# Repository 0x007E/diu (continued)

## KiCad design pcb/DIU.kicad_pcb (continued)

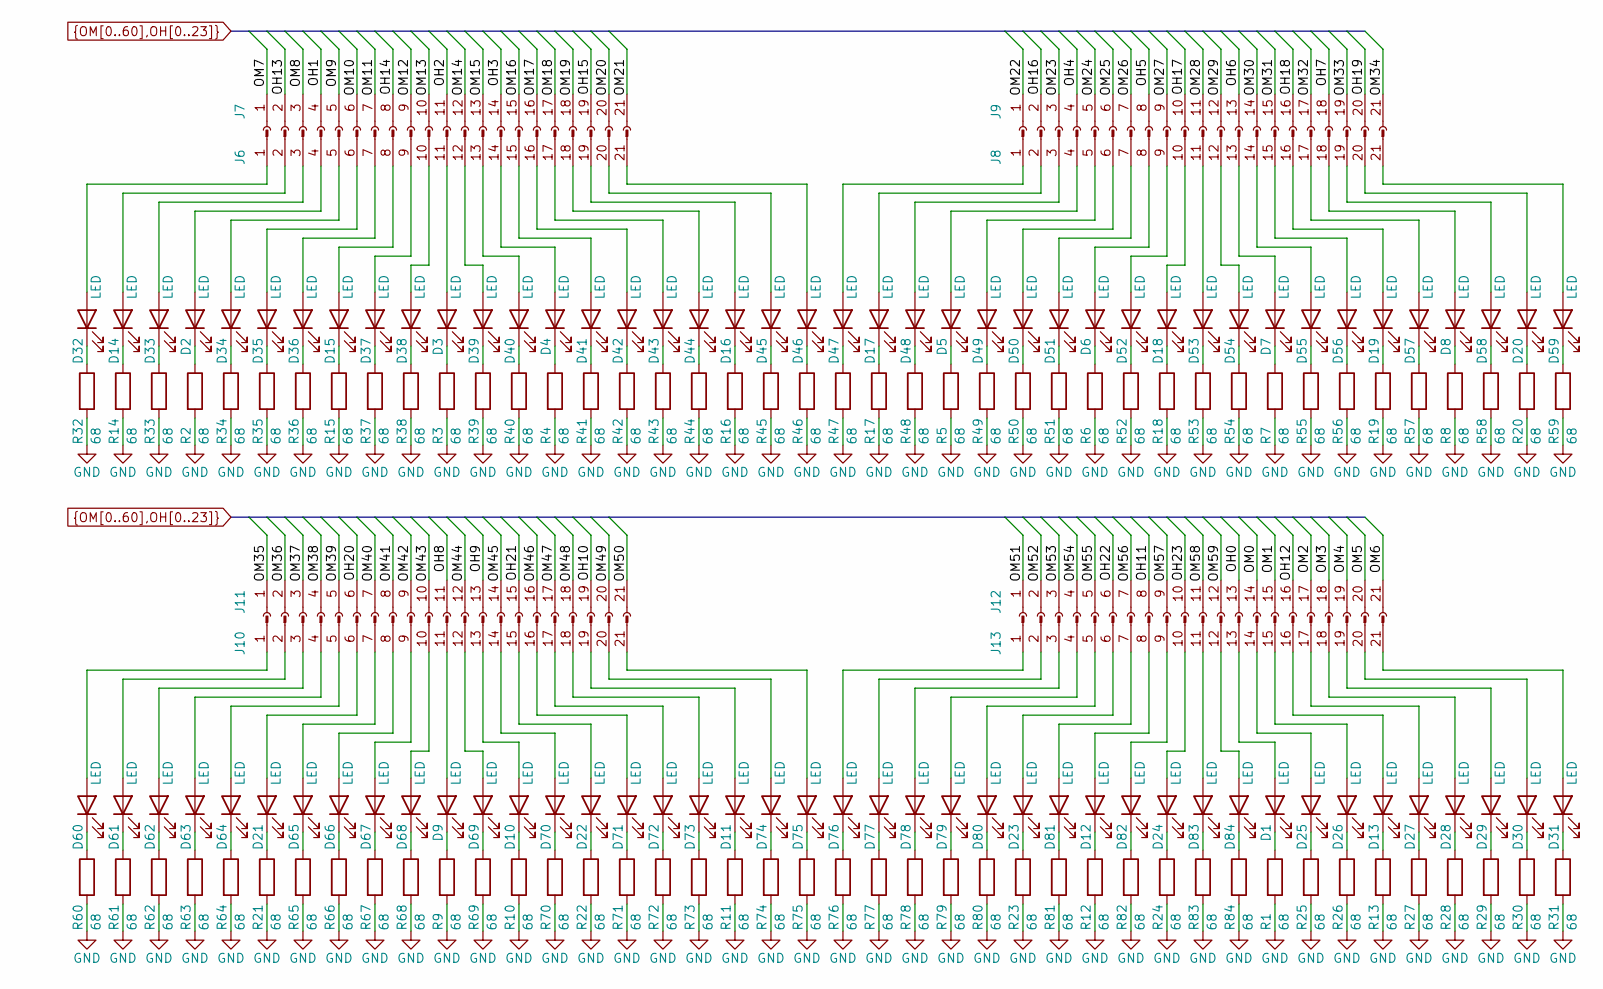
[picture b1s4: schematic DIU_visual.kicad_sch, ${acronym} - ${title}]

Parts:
D1, D2, D3, D4, D5, D6, D7, D8, D9, D10, D11, D12, D13, D14, D15, D16, D17, D18, D19, D20, D21, D22, D23, D24, D25, D26, D27, D28, D29, D30, D31, D32, D33, D34, D35, D36, D37, D38, D39, D40, D41, D42, D43, D44, D45, D46, D47, D48, D49, D50, D51, D52, D53, D54, D55, D56, D57, D58, D59, D60, D61, D62, D63, D64, D65, D66, D67, D68, D69, D70, D71, D72, D73, D74, D75, D76, D77, D78, D79, D80, D81, D82, D83, D84: LED; LED_1206_3216Metric
J6, J8, J10, J13: Conn_01x21_Pin; PinHeader_1x21_P2.54mm_Vertical
J7, J9, J11, J12: Conn_01x21_Socket; PinSocket_1x21_P2.54mm_Vertical
R1, R2, R3, R4, R5, R6, R7, R8, R9, R10, R11, R12, R13, R14, R15, R16, R17, R18, R19, R20, R21, R22, R23, R24, R25, R26, R27, R28, R29, R30, R31, R32, R33, R34, R35, R36, R37, R38, R39, R40, R41, R42, R43, R44, R45, R46, R47, R48, R49, R50, R51, R52, R53, R54, R55, R56, R57, R58, R59, R60, R61, R62, R63, R64, R65, R66, R67, R68, R69, R70, R71, R72, R73, R74, R75, R76, R77, R78, R79, R80, R81, R82, R83, R84: 68; R_1206_3216Metric

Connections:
GND: R1.2, R2.2, R3.2, R4.2, R5.2, R6.2, R7.2, R8.2, R9.2, R10.2, R11.2, R12.2, R13.2, R14.2, R15.2, R16.2, R17.2, R18.2, R19.2, R20.2, R21.2, R22.2, R23.2, R24.2, R25.2, R26.2, R27.2, R28.2, R29.2, R30.2, R31.2, R32.2, R33.2, R34.2, R35.2, R36.2, R37.2, R38.2, R39.2, R40.2, R41.2, R42.2, R43.2, R44.2, R45.2, R46.2, R47.2, R48.2, R49.2, R50.2, R51.2, R52.2, R53.2, R54.2, R55.2, R56.2, R57.2, R58.2, R59.2, R60.2, R61.2, R62.2, R63.2, R64.2, R65.2, R66.2, R67.2, R68.2, R69.2, R70.2, R71.2, R72.2, R73.2, R74.2, R75.2, R76.2, R77.2, R78.2, R79.2, R80.2, R81.2, R82.2, R83.2, R84.2; also elsewhere on the board
unnamed: D1.2 (A), J13.13
unnamed: D1.1 (K), R1.1
unnamed: D2.2 (A), J6.4
unnamed: D2.1 (K), R2.1
unnamed: D3.2 (A), J6.11
unnamed: D3.1 (K), R3.1
unnamed: D4.2 (A), J6.14
unnamed: D4.1 (K), R4.1
unnamed: D5.2 (A), J8.4
unnamed: D5.1 (K), R5.1
unnamed: D6.2 (A), J8.8
unnamed: D6.1 (K), R6.1
unnamed: D7.2 (A), J8.13
unnamed: D7.1 (K), R7.1
unnamed: D8.2 (A), J8.18
unnamed: D8.1 (K), R8.1
unnamed: D9.2 (A), J10.11
unnamed: D9.1 (K), R9.1
unnamed: D10.2 (A), J10.13
unnamed: D10.1 (K), R10.1
unnamed: D11.2 (A), J10.19
unnamed: D11.1 (K), R11.1
unnamed: D12.2 (A), J13.8
unnamed: D12.1 (K), R12.1
unnamed: D13.2 (A), J13.16
unnamed: D13.1 (K), R13.1
unnamed: D14.2 (A), J6.2
unnamed: D14.1 (K), R14.1
unnamed: D15.2 (A), J6.8
unnamed: D15.1 (K), R15.1
unnamed: D16.2 (A), J6.19
unnamed: D16.1 (K), R16.1
unnamed: D17.2 (A), J8.2
unnamed: D17.1 (K), R17.1
unnamed: D18.2 (A), J8.10
unnamed: D18.1 (K), R18.1
unnamed: D19.2 (A), J8.16
unnamed: D19.1 (K), R19.1
unnamed: D20.2 (A), J8.20
unnamed: D20.1 (K), R20.1
unnamed: D21.2 (A), J10.6
unnamed: D21.1 (K), R21.1
unnamed: D22.2 (A), J10.15
unnamed: D22.1 (K), R22.1
unnamed: D23.2 (A), J13.6
unnamed: D23.1 (K), R23.1
unnamed: D24.2 (A), J13.10
unnamed: D24.1 (K), R24.1
unnamed: D25.2 (A), J13.14
unnamed: D25.1 (K), R25.1
unnamed: D26.2 (A), J13.15
unnamed: D26.1 (K), R26.1
unnamed: D27.2 (A), J13.17
unnamed: D27.1 (K), R27.1
unnamed: D28.2 (A), J13.18
unnamed: D28.1 (K), R28.1
unnamed: D29.2 (A), J13.19
unnamed: D29.1 (K), R29.1
unnamed: D30.2 (A), J13.20
unnamed: D30.1 (K), R30.1
unnamed: D31.2 (A), J13.21
unnamed: D31.1 (K), R31.1
unnamed: D32.2 (A), J6.1
unnamed: D32.1 (K), R32.1
unnamed: D33.2 (A), J6.3
unnamed: D33.1 (K), R33.1
unnamed: D34.2 (A), J6.5
unnamed: D34.1 (K), R34.1
unnamed: D35.2 (A), J6.6
unnamed: D35.1 (K), R35.1
unnamed: D36.2 (A), J6.7
unnamed: D36.1 (K), R36.1
unnamed: D37.2 (A), J6.9
unnamed: D37.1 (K), R37.1
unnamed: D38.2 (A), J6.10
unnamed: D38.1 (K), R38.1
unnamed: D39.2 (A), J6.12
unnamed: D39.1 (K), R39.1
unnamed: D40.2 (A), J6.13
unnamed: D40.1 (K), R40.1
unnamed: D41.2 (A), J6.15
unnamed: D41.1 (K), R41.1
unnamed: D42.2 (A), J6.16
unnamed: D42.1 (K), R42.1
unnamed: D43.2 (A), J6.17
unnamed: D43.1 (K), R43.1
unnamed: D44.2 (A), J6.18
unnamed: D44.1 (K), R44.1
unnamed: D45.2 (A), J6.20
unnamed: D45.1 (K), R45.1
unnamed: D46.2 (A), J6.21
unnamed: D46.1 (K), R46.1
unnamed: D47.2 (A), J8.1
unnamed: D47.1 (K), R47.1
unnamed: D48.2 (A), J8.3
unnamed: D48.1 (K), R48.1
unnamed: D49.2 (A), J8.5
unnamed: D49.1 (K), R49.1
unnamed: D50.2 (A), J8.6
unnamed: D50.1 (K), R50.1
unnamed: D51.2 (A), J8.7
unnamed: D51.1 (K), R51.1
unnamed: D52.2 (A), J8.9
unnamed: D52.1 (K), R52.1
unnamed: D53.2 (A), J8.11
unnamed: D53.1 (K), R53.1
unnamed: D54.2 (A), J8.12
unnamed: D54.1 (K), R54.1
unnamed: D55.2 (A), J8.14
unnamed: D55.1 (K), R55.1
unnamed: D56.2 (A), J8.15
unnamed: D56.1 (K), R56.1
unnamed: D57.2 (A), J8.17
unnamed: D57.1 (K), R57.1
unnamed: D58.2 (A), J8.19
unnamed: D58.1 (K), R58.1
unnamed: D59.2 (A), J8.21
unnamed: D59.1 (K), R59.1
unnamed: D60.2 (A), J10.1
unnamed: D60.1 (K), R60.1
unnamed: D61.2 (A), J10.2
unnamed: D61.1 (K), R61.1
unnamed: D62.2 (A), J10.3
unnamed: D62.1 (K), R62.1
unnamed: D63.2 (A), J10.4
unnamed: D63.1 (K), R63.1
unnamed: D64.2 (A), J10.5
unnamed: D64.1 (K), R64.1
unnamed: D65.2 (A), J10.7
unnamed: D65.1 (K), R65.1
unnamed: D66.2 (A), J10.8
unnamed: D66.1 (K), R66.1
unnamed: D67.2 (A), J10.9
unnamed: D67.1 (K), R67.1
unnamed: D68.2 (A), J10.10
unnamed: D68.1 (K), R68.1
unnamed: D69.2 (A), J10.12
unnamed: D69.1 (K), R69.1
unnamed: D70.2 (A), J10.14
unnamed: D70.1 (K), R70.1
unnamed: D71.2 (A), J10.16
unnamed: D71.1 (K), R71.1
unnamed: D72.2 (A), J10.17
unnamed: D72.1 (K), R72.1
unnamed: D73.2 (A), J10.18
unnamed: D73.1 (K), R73.1
unnamed: D74.2 (A), J10.20
unnamed: D74.1 (K), R74.1
unnamed: D75.2 (A), J10.21
unnamed: D75.1 (K), R75.1
unnamed: D76.2 (A), J13.1
unnamed: D76.1 (K), R76.1
unnamed: D77.2 (A), J13.2
unnamed: D77.1 (K), R77.1
unnamed: D78.2 (A), J13.3
unnamed: D78.1 (K), R78.1
unnamed: D79.2 (A), J13.4
unnamed: D79.1 (K), R79.1
unnamed: D80.2 (A), J13.5
unnamed: D80.1 (K), R80.1
unnamed: D81.2 (A), J13.7
unnamed: D81.1 (K), R81.1
unnamed: D82.2 (A), J13.9
unnamed: D82.1 (K), R82.1
unnamed: D83.2 (A), J13.11
unnamed: D83.1 (K), R83.1
unnamed: D84.2 (A), J13.12
unnamed: D84.1 (K), R84.1
OH0: J12.13; also elsewhere on the board
OH1: J7.4; also elsewhere on the board
OH2: J7.11; also elsewhere on the board
OH3: J7.14; also elsewhere on the board
OH4: J9.4; also elsewhere on the board
OH5: J9.8; also elsewhere on the board
OH6: J9.13; also elsewhere on the board
OH7: J9.18; also elsewhere on the board
OH8: J11.11; also elsewhere on the board
OH9: J11.13; also elsewhere on the board
OH10: J11.19; also elsewhere on the board
OH11: J12.8; also elsewhere on the board
OH12: J12.16; also elsewhere on the board
OH13: J7.2; also elsewhere on the board
OH14: J7.8; also elsewhere on the board
OH15: J7.19; also elsewhere on the board
OH16: J9.2; also elsewhere on the board
OH17: J9.10; also elsewhere on the board
OH18: J9.16; also elsewhere on the board
OH19: J9.20; also elsewhere on the board
OH20: J11.6; also elsewhere on the board
OH21: J11.15; also elsewhere on the board
OH22: J12.6; also elsewhere on the board
OH23: J12.10; also elsewhere on the board
OM0: J12.14; also elsewhere on the board
OM1: J12.15; also elsewhere on the board
OM2: J12.17; also elsewhere on the board
OM3: J12.18; also elsewhere on the board
OM4: J12.19; also elsewhere on the board
OM5: J12.20; also elsewhere on the board
OM6: J12.21; also elsewhere on the board
OM7: J7.1; also elsewhere on the board
OM8: J7.3; also elsewhere on the board
OM9: J7.5; also elsewhere on the board
OM10: J7.6; also elsewhere on the board
OM11: J7.7; also elsewhere on the board
OM12: J7.9; also elsewhere on the board
OM13: J7.10; also elsewhere on the board
OM14: J7.12; also elsewhere on the board
OM15: J7.13; also elsewhere on the board
OM16: J7.15; also elsewhere on the board
OM17: J7.16; also elsewhere on the board
OM18: J7.17; also elsewhere on the board
OM19: J7.18; also elsewhere on the board
OM20: J7.20; also elsewhere on the board
OM21: J7.21; also elsewhere on the board
OM22: J9.1; also elsewhere on the board
OM23: J9.3; also elsewhere on the board
OM24: J9.5; also elsewhere on the board
OM25: J9.6; also elsewhere on the board
OM26: J9.7; also elsewhere on the board
OM27: J9.9; also elsewhere on the board
OM28: J9.11; also elsewhere on the board
OM29: J9.12; also elsewhere on the board
OM30: J9.14; also elsewhere on the board
OM31: J9.15; also elsewhere on the board
OM32: J9.17; also elsewhere on the board
OM33: J9.19; also elsewhere on the board
OM34: J9.21; also elsewhere on the board
OM35: J11.1; also elsewhere on the board
OM36: J11.2; also elsewhere on the board
OM37: J11.3; also elsewhere on the board
OM38: J11.4; also elsewhere on the board
OM39: J11.5; also elsewhere on the board
OM40: J11.7; also elsewhere on the board
OM41: J11.8; also elsewhere on the board
OM42: J11.9; also elsewhere on the board
OM43: J11.10; also elsewhere on the board
OM44: J11.12; also elsewhere on the board
OM45: J11.14; also elsewhere on the board
OM46: J11.16; also elsewhere on the board
OM47: J11.17; also elsewhere on the board
OM48: J11.18; also elsewhere on the board
OM49: J11.20; also elsewhere on the board
OM50: J11.21; also elsewhere on the board
OM51: J12.1; also elsewhere on the board
OM52: J12.2; also elsewhere on the board
OM53: J12.3; also elsewhere on the board
OM54: J12.4; also elsewhere on the board
OM55: J12.5; also elsewhere on the board
OM56: J12.7; also elsewhere on the board
OM57: J12.9; also elsewhere on the board
OM58: J12.11; also elsewhere on the board
OM59: J12.12; also elsewhere on the board

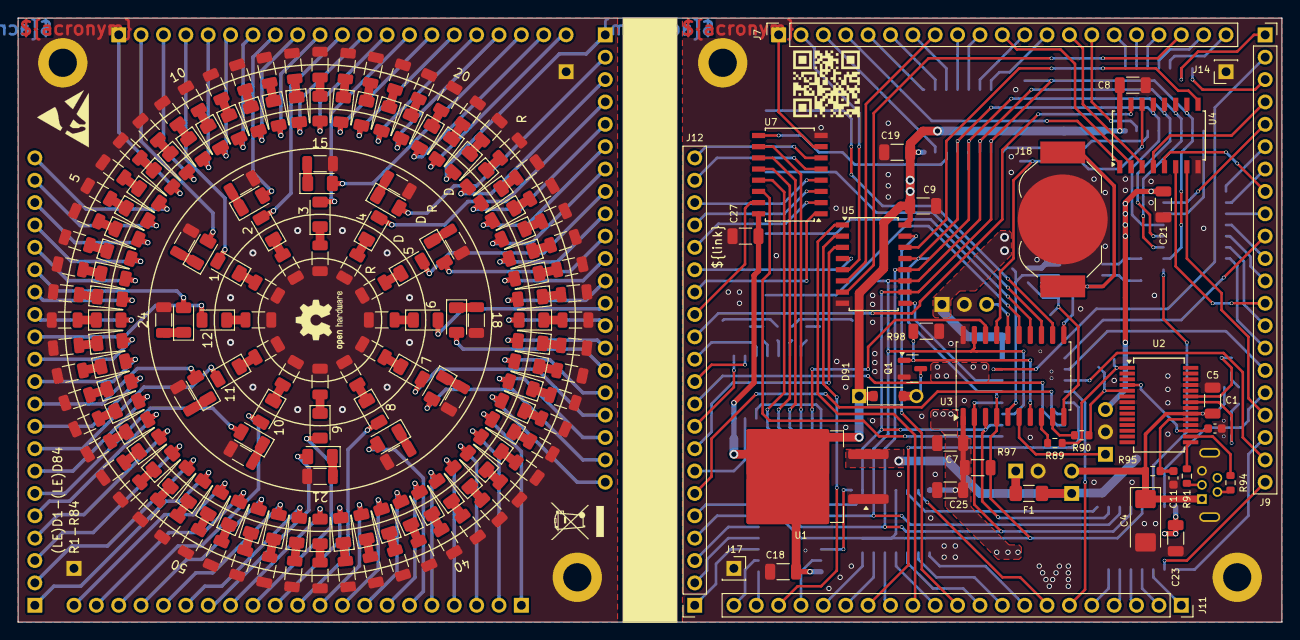
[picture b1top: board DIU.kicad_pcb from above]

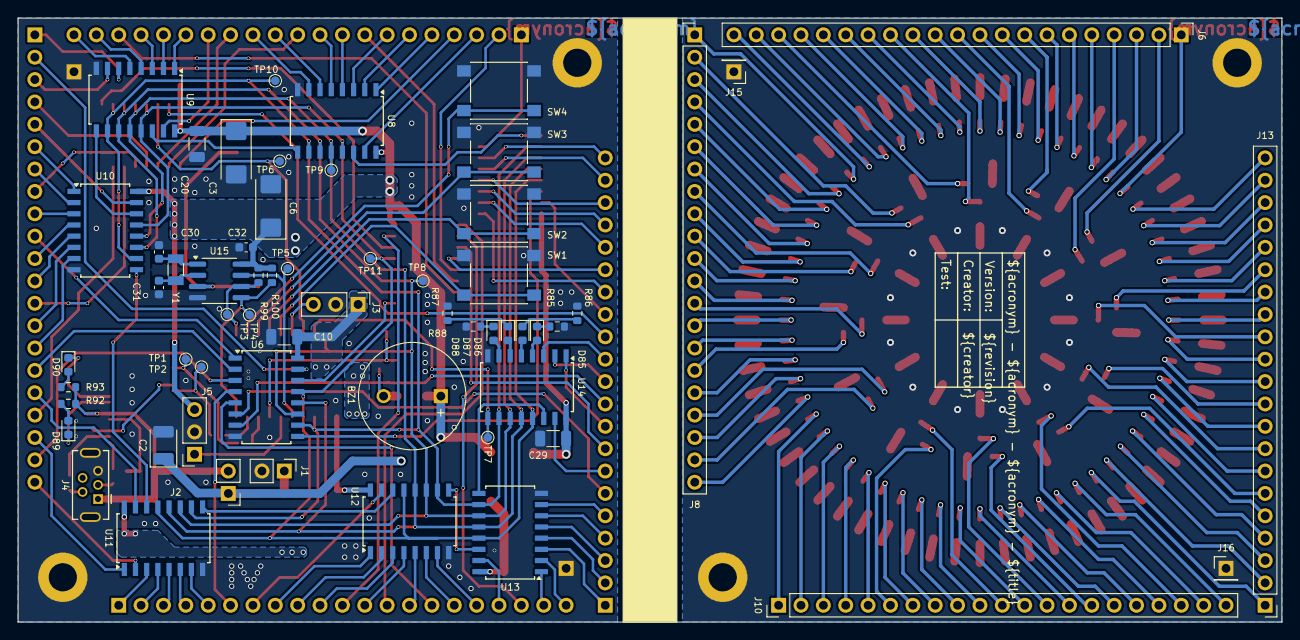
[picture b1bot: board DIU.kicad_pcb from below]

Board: 2 copper layers, 143.5 x 68.6 mm, 272 parts (60 on the bottom side), 309 nets.

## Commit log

2024-11-01 Add README
2024-11-01 Create pipeline
2024-11-01 Fix color settings
2024-11-01 Fix wrong filename
2024-11-01 Change config
2025-09-13 Partlist refactoring
2025-09-13 Change reset circuit
2025-09-13 Fix footprint reference match problem
2025-09-13 Change silkscreen text size
2025-09-13 Add missing 3d models
2025-09-13 Change action badge
2025-09-13 Extend readability
2025-09-13 Add firmware badge
2025-09-13 Increase FreeCAD version
2025-09-13 Add value to BOM
2025-09-14 Add resistor to reset circuit
2025-09-14 Rearrange text on fabrication layer
2025-09-15 Add system testing firmware
2025-09-15 Add build of test-firmware
2025-09-15 Add test firmware download link
2025-10-16 Extend exploded assembly
2025-10-23 Fix firmware copy bug
2025-10-23 Add missing artifact upload
2025-10-24 Fix wrong F_CPU value
2025-10-24 Remove clause that does not guard
2025-10-24 Change firmware build workflow
2025-10-24 Format firmware build workflow
2025-10-24 Change firmware release workflow
2025-10-29 Add DeepWiki badge
2026-01-28 Fix wrong led polarity
2026-01-28 Adapt vendor-ids on leds
2026-02-06 Add missing dependency
